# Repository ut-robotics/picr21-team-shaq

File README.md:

# Project in Competitive Robotics 2021 (Shaq team)

This repository contains code for the course "Project in Competitive Robotics" of team "Shaq"

## Running the code

The code runs on a computer located on the robot, so some kind of remote connection (ssh, for example) with it is required. If SSH is used and seeing processed images is required, then SSH connection should be established with X forwarding enabled:

```
ssh -X [username]@[host]
```

Before running game code itself, it is advised to calibrate detection of different colors.

### Calibration

To calibrate detection of a color, move to **tests** directory and run **calibrate.py** file along with desired color as an argument.

For example for calibrating green color, run this:

```
cd tests/
python3 calibrate.py green
```

*Note*: If your computer is relatively old, then it's advised not to run calibration remotely, but disconnect the camera from robot's computer, connect it to your computer and run script locally.

### Running WebSocket server

The robot depends on referee server to provide info about color of target basket and when to start or stop. By default robot will not do anything until it receives start signal directed to it. Therefore, unless some other WebSocket server is already provided, WebSocket server will need to be run before running the game code.

Move to **src** directory. Before running the server, open the file and change the value of *ipaddr* value to IP address of machine running the server. The port generally need not be changed. Run **server.py** file. Until client is connected it will not ouput anything. Once client successfully connected, you will be prompted to enter either **start** or **stop** to send appropriate signals. The content of both signals is contained in **config** directory as **referee_start.json** and **referee_stop.json** files which can be edited manually. Refer [here](https://github.com/ut-robotics/robot-basketball-manager) for more info on signals.

### Running game logic

Before running the code make sure that camera is connected to the robot computer and the mainboard is turned on.

Move to the **src** directory.

Game code is ran from **main.py** file. Before running the code, edit *referee_ip* variable to the IP-address of your WebSocket server and *robot_name* variable to the name used to identify your robot. Since the communication with the mainboard requires root, **main.py** and all files using *Communication* and *Movement* classes needs to be ran with root privileges:

```
sudo python3 main.py
```

However, if SSH is used and seeing images is also required, then SSH connection will need to be established with a **root** user first, and the file will need to be ran as a root user.

```
python3 main.py
```

If you do not need to output the images, comment following lines near the end of main try-block out:

```
cv2.imshow("View", frame)
cv2.imshow("Balls", ball_mask)
```

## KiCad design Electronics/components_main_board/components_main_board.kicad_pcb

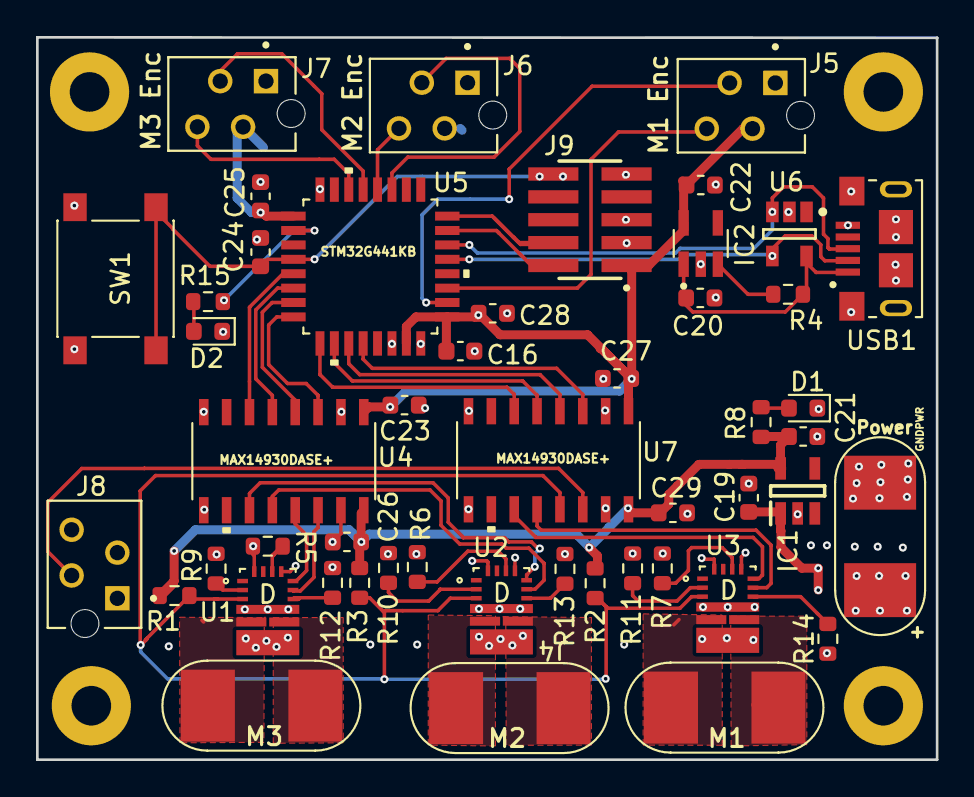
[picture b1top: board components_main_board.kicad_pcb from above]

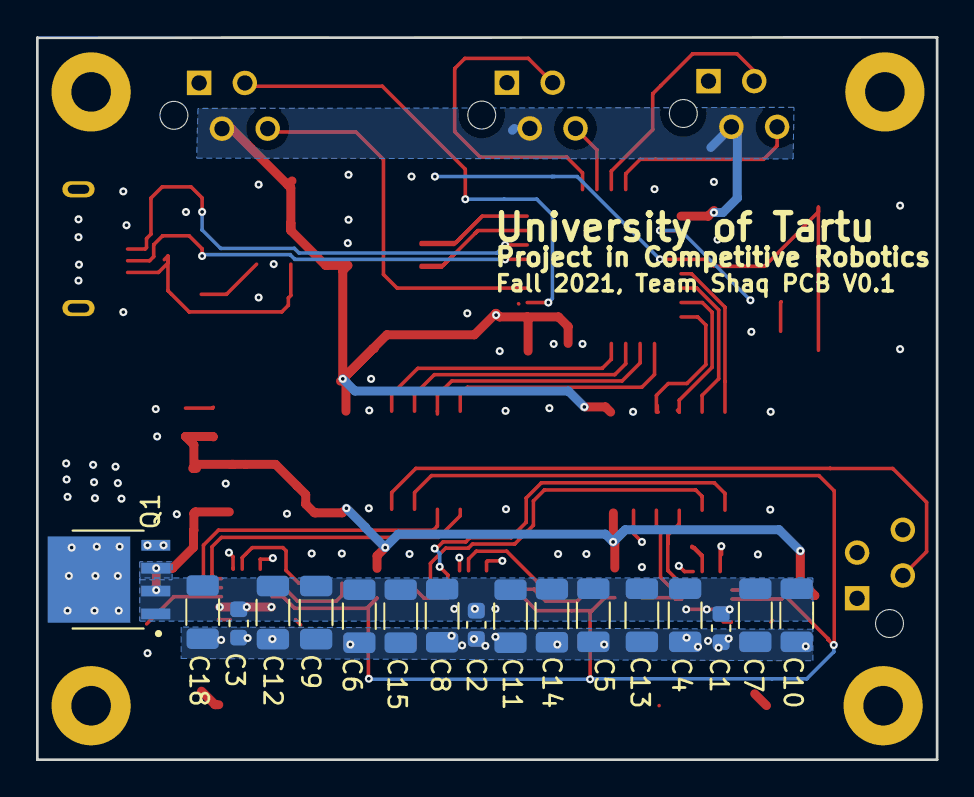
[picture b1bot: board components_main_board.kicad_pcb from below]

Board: 4 copper layers, 50.0 x 40.1 mm, 70 parts (17 on the bottom side), 53 nets.

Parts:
C1, C2, C3, C23, C24, C26, C27, C29: 0.1μF; C_0603_1608Metric
C4, C5, C6, C7, C8, C9, C10, C11, C12, C13, C14, C15, C18: 10μF; C_1206_3216Metric
C16, C25, C28: 100nF; C_0603_1608Metric
C19, C20, C21, C22: 1μF; C_0603_1608Metric
D1, D2: LED; D_0603_1608Metric
H1, H2, H3, H4: H; MountingHole_2.2mm_M2_Pad
IC1: NCV8730ASN500T1G; SOT95P275X110-5N
IC2: NCP164CSN330T1G; SOP95P275X110-5N
J1: Power; Banana_Jack_2Pin_New_1
J2: M3; Banana_Jack_2Pin_New_1
J3: M1; Banana_Jack_2Pin_New_1
J4: M2; Banana_Jack_2Pin_New_1
J5, J6, J7, J8: 215079-4; TE_215079-4
J9: FTSH-105; SAMTEC_FTSH-105-XX-X-DV
Q1: BUK6Y10-30P; TO127P600X120-5N
R1, R2, R3, R4, R12, R13, R14: 10K; R_0603_1608Metric
R5, R6, R7: 100K; R_0603_1608Metric
R8, R9, R10, R11, R15: 3.3K; R_0603_1608Metric
SW1: SW_Push; SW_Push_1P1T_NO_6x6mm_H9.5mm
U1, U2, U3: DRV8243-Q1; PDRV8243HRXYQ1
U4, U7: MAX14930DASE+; MAX14930DASE&plus_
U5: STM32G441KB; STM32G441KBT3
U6: CM1223; On_Semiconductor-CM1223-02SO-Level_A
USB1: 10118193-0001LF-Amphenol_10118193-0001LF; FCI_10118193-0001LF

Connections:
+3V3: C16.1, C22.1, C23.2, C25.2, C27.2, C28.1, IC2.5, J5.2, J6.2, J7.2, J9.01, U4.1, U5.1, U5.15, U5.17, U7.1
+5C: C20.1, IC2.1, R4.2, U6.5, USB1.1
+5V: C21.1, C26.1, C29.1, IC1.5, R1.2, R2.1, R3.1, R8.2, U4.16, U7.16
+15V: C1.1, C2.1, C3.1, C4.1, C5.1, C6.1, C7.1, C8.1, C9.1, C10.1, C11.1, C12.1, C13.1, C14.1, C15.1, C18.1, C19.1, IC1.1, Q1.1, Q1.2, Q1.3, U1.4, U2.4, U3.4
DRVOFF_M1: R12.1, U1.8
DRVOFF_M2: R13.1, U2.8
DRVOFF_M3: R14.1, U3.8
GND: C16.2, C20.2, C22.2, C23.1, C24.2, C25.1, C27.1, C28.2, D2.1, IC2.2, J5.1, J6.1, J7.1, J9.03, J9.05, J9.09, SW1.2, U4.2, U4.8, U5.14, U5.16, U5.32, U6.2, U7.2, U7.8, USB1.5, USB1.S1, USB1.S2, USB1.S3, USB1.S4, USB1.S5, USB1.S6
GNDPWR: C1.2, C2.2, C3.2, C4.2, C5.2, C6.2, C7.2, C8.2, C9.2, C10.2, C11.2, C12.2, C13.2, C14.2, C15.2, C18.2, C19.2, C21.2, C26.2, C29.2, D1.1, IC1.2, J1.2, J8.1, Q1.4, R5.1, R6.1, R7.1, R9.1, R10.1, R11.1, R12.2, R13.2, R14.2, U1.6, U1.11, U1.14, U2.6, U2.11, U2.14, U3.6, U3.11, U3.14, U4.9, U4.15, U7.9, U7.15
IC1_EN: IC2.3, R4.1
IPROPI_M1: R9.2, U1.2
IPROPI_M2: R10.2, U2.2
IPROPI_M3: R11.2, U3.2
Led: R15.1, U5.2
M1_Dir: U4.4, U5.7
M1_Dir_Driver: U1.10, U4.13
M1_Encoder_CH1: J5.3, U5.18
M1_Encoder_CH2: J5.4, U5.19
M1_Out1: J3.1, U1.7
M1_Out2: J3.2, U1.5
M1_PWM: U4.3, U5.8
M1_PWM_Driver: U1.9, U4.14
M2_Dir: U4.6, U5.5
M2_Dir_Driver: U2.10, U4.11
M2_Encoder_CH1: J6.3, U5.27
M2_Encoder_CH2: J6.4, U5.28
M2_Out1: J4.1, U2.7
M2_Out2: J4.2, U2.5
M2_PWM: U4.5, U5.6
M2_PWM_Driver: U2.9, U4.12
M3_Dir: U5.9, U7.6
M3_Dir_Driver: U3.10, U7.11
M3_Encoder_CH1: J7.3, U5.29
M3_Encoder_CH2: J7.4, U5.30
M3_Out1: J2.1, U3.7
M3_Out2: J2.2, U3.5
M3_PWM: U5.10, U7.5
M3_PWM_Driver: U3.9, U7.12
MCU_nSleep_Isol: U5.11, U7.4
NRST: C24.1, J9.10, SW1.1, U5.4
unnamed: D1.2, R8.1
unnamed: D2.2, R15.2
unnamed: J1.1, Q1.5
Programmer_Clk: J9.04, U5.24
Programmer_DIO: J9.02, U5.23
SR_M1: R5.2, U1.12
SR_M2: R6.2, U2.12
SR_M3: R7.2, U3.12
Thrower_PWM: U5.12, U7.3
Thrower_PWM_Out: J8.2, U7.14
USB_DM: U5.21, U6.4, USB1.2
USB_DP: U5.22, U6.3, USB1.3
nSleep_Driv: R1.1, R2.2, R3.2, U1.3, U2.3, U3.3, U7.13

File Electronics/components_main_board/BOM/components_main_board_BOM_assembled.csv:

Id,Designator,Package,Quantity,Designation,On PCB,
1,"FD2,FD1",Fiducial_0.5mm_Mask1.5mm,2,Fiducial_0.5mm_Mask1.5mm,,
2,"U4,U7",MAX14930DASE&plus_,2,MAX14930DASE+,Yes,
3,U5,STM32G441KBT3,1,STM32G441KB,Yes,
4,"H4,H3,H2,H1",MountingHole_2.2mm_M2_Pad,4,H,,
5,USB1,FCI_10118193-0001LF,1,10118193-0001LF-Amphenol_10118193-0001LF,Yes,
6,U6,On_Semiconductor-CM1223-02SO-Level_A,1,CM1223,Yes,
7,Q1,TO127P600X120-5N,1,BUK6Y10-30P,Yes,
8,J9,SAMTEC_FTSH-105-XX-X-DV,1,FTSH-105,Yes,
9,"Thrower,J2,J4,J3",TE_215079-4,4,215079-4,,
10,J4,Banana_Jack_2Pin_New_1,1,M2,,
11,J3,Banana_Jack_2Pin_New_1,1,M1,,
12,J2,Banana_Jack_2Pin_New_1,1,M3,,
13,J1,Banana_Jack_2Pin_New_1,1,Power,,
14,IC2,SOP95P275X110-5N,1,NCP164CSN330T1G,Yes,
15,"D2,D1",D_0603_1608Metric,2,LED,,"D2, D1"
16,"C18,C17,C16,C15,C14, 
C13,C12,C11,C10,C9
C8,C7,C6,C5,C4",C_0603_1608Metric,15,10μF,Yes,"C16, C18, C12, C9, C6, C15
C8"
17,"R14,R13,R12,R3,R2,R1,R4",R_0603_1608Metric,7,10K,,"R14, R4, R13, R2, R12, R3, R1"
18,"R8,R15,R11,R10,R9",R_0603_1608Metric,5,3.3K,,"R15, R8, R11, R10, R9"
19,"R5,R7,R6",R_0603_1608Metric,3,100K,,"R7, R6, R5"
20,"C19,C21,C22,C20",C_0603_1608Metric,4,1μF,,"C20, C22, C21, C19"
21,"C26,C3,C29,C1,C23,C27,C24,C2",C_0603_1608Metric,8,0.1μF,,"C24, C23, C27, C29, C26"
22,"C28,C25",C_0603_1608Metric,2,100nF,Yes,"C25, C28"
23,IC1,SOT95P275X110-5N,1,NCV8730ASN500T1G,Yes,
24,SW1,SW_Push_1P1T_NO_6x6mm_H9.5mm,1,SW_Push,,
25,"U2,U1,U3",PDRV8243HRXYQ1,3,DRV8243,Yes,

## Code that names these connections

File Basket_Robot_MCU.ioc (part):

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Mcu.Name=STM32G441KBTx
Mcu.Package=LQFP32
Mcu.UserName=STM32G441KBTx
PA0.GPIOParameters=GPIO_Label
PA0.GPIO_Label=M2_Direction
PA0.Signal=GPIO_Output
PA1.GPIOParameters=GPIO_Label
PA1.GPIO_Label=M2_PWM
PA1.Signal=S_TIM2_CH2
PA11.Mode=Device
PA11.Signal=USB_DM
PA12.Mode=Device
PA12.Signal=USB_DP
PA13.Mode=Serial_Wire
PA13.Signal=SYS_JTMS-SWDIO
PA14.Mode=Serial_Wire
PA14.Signal=SYS_JTCK-SWCLK
PA2.GPIOParameters=GPIO_Label
PA2.GPIO_Label=M1_Direction
PA2.Signal=GPIO_Output
PA3.GPIOParameters=GPIO_Label
PA3.GPIO_Label=M1_PWM
PA3.Signal=S_TIM2_CH4
PA4.GPIOParameters=GPIO_Label
PA4.GPIO_Label=M3_Direction
PA4.Signal=GPIO_Output
PA5.GPIOParameters=GPIO_Label
PA5.GPIO_Label=M3_PWM
PA5.Signal=S_TIM2_CH1
PA6.GPIOParameters=GPIO_Label
PA6.GPIO_Label=n_Sleep
PA6.Signal=S_TIM16_CH1
PA7.GPIOParameters=GPIO_Label
PA7.GPIO_Label=Thrower_PWM
PA7.Signal=S_TIM17_CH1
PA8.Signal=S_TIM1_CH1
PA9.Signal=S_TIM1_CH2
PB4.Signal=S_TIM3_CH1
PB5.Signal=S_TIM3_CH2
PB6.Signal=S_TIM4_CH1
PB7.Signal=S_TIM4_CH2
PF0-OSC_IN.GPIOParameters=GPIO_Speed,GPIO_Label
PF0-OSC_IN.GPIO_Label=Led
PF0-OSC_IN.GPIO_Speed=GPIO_SPEED_FREQ_MEDIUM
PF0-OSC_IN.Signal=GPIO_Output
RCC.HSE_VALUE=8000000
RCC.SYSCLKFreq_VALUE=160000000
RCC.SYSCLKSource=RCC_SYSCLKSOURCE_PLLCLK
board=custom

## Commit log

2021-09-09 initial code for mainboard communication (sending the commands)
2021-09-12 added logic for receiving from mainboard, added threading, changed the structure of code somewhat
2021-09-13 exploration
2021-09-17 obj detection in progress
2021-09-20 Img processing threads
2021-09-22 moved to src/ directory
2021-09-30 RealSense & detection modifications
2021-10-11 minor fixes
2021-10-24 fixed small issues
2021-10-25 printing ball coordinates
2021-10-25 printing str instead of int
2021-10-28 new version of comm.py
2021-11-07 added descriptions of motor speeds for moving to various directions
2021-11-08 calibration program now works, added speeds for directions to move according to position of the ball
2021-11-09 keyboard stuff
2021-11-11 updated speeds
2021-11-17 about to test this stuff
2021-11-19 move
2021-11-19 working?
2021-11-22 robot is now moving according to position of the ball
2021-11-22 working on driving
2021-11-27 image processing update
2021-11-27 hope this doesn't kill the robot
2021-12-03 inefficient & unreliable & not working line detection
2021-12-06 Moved state logic and related stuff from communication to a separate file, previous variant moved to comm_old
2021-12-06 variable name to lower case
2021-12-08 state machine base && detection stuff
2022-01-03 serial port now being found using list_ports
2022-01-03 commObject created only once
2022-01-03 added delay to send speeds less often
2022-01-03 trying to fix merge conflicts
2022-01-10 Trying to simplify
2022-01-11 Custom message
2022-01-12 hsdjfhsjkdkj
2022-01-13 some primitive throwing stuff
2022-01-13 small success rate autonomous throwing
2022-01-14 now finding needed port by product string of a mainboard
2022-01-15 added script for demonstrating the task 2
2022-01-16 states now handled by separate functions
2022-01-17 Revert "states now handled by separate functions"
    This reverts commit 94c7377ab6a151a2c8679eadbd48acfd353b746e.
2022-01-17 will revert to functions later
2022-01-17 hopefully better ball filtering && throwing centering
2022-01-17 decent throwing potential
2022-01-19 added very simple client and server
2022-01-19 small changes
2022-01-19 Client class created, but needs to be improved
2022-01-19 äääääääääääääääääää
2022-01-19 tried something
2022-01-20 now getting info from client using queue
2022-01-20 WebSocket client is now usable within main game code
2022-01-20 base state, rotational movements, camera settings
2022-01-21 added new state STOP to be the default state and when robot receives a stop signal
2022-01-21 various small changes
2022-01-21 various changes
2022-01-22 Base state + simultaenous movement and rotation
2022-01-23 Create Electronics
2022-01-23 Electronics Schematics
2022-01-23 Firmware
2022-01-23 Electronics and Firmware
2022-01-23 electrocnics and firmware
2022-01-24 Line sampler
2022-01-24 LINE DETECTION WORKSgit status!
2022-01-24 24.01
2022-01-24 Schematic and BOM files added
2022-01-25 More understandable if
2022-01-25 .cproject .mxproject and .project files added to repos
2022-01-25 updated .gitignore file on Debug folder
2022-01-27 created README

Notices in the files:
parts and their libraries:
Copyright 2021 Accelerated Designs. All rights reserved.
